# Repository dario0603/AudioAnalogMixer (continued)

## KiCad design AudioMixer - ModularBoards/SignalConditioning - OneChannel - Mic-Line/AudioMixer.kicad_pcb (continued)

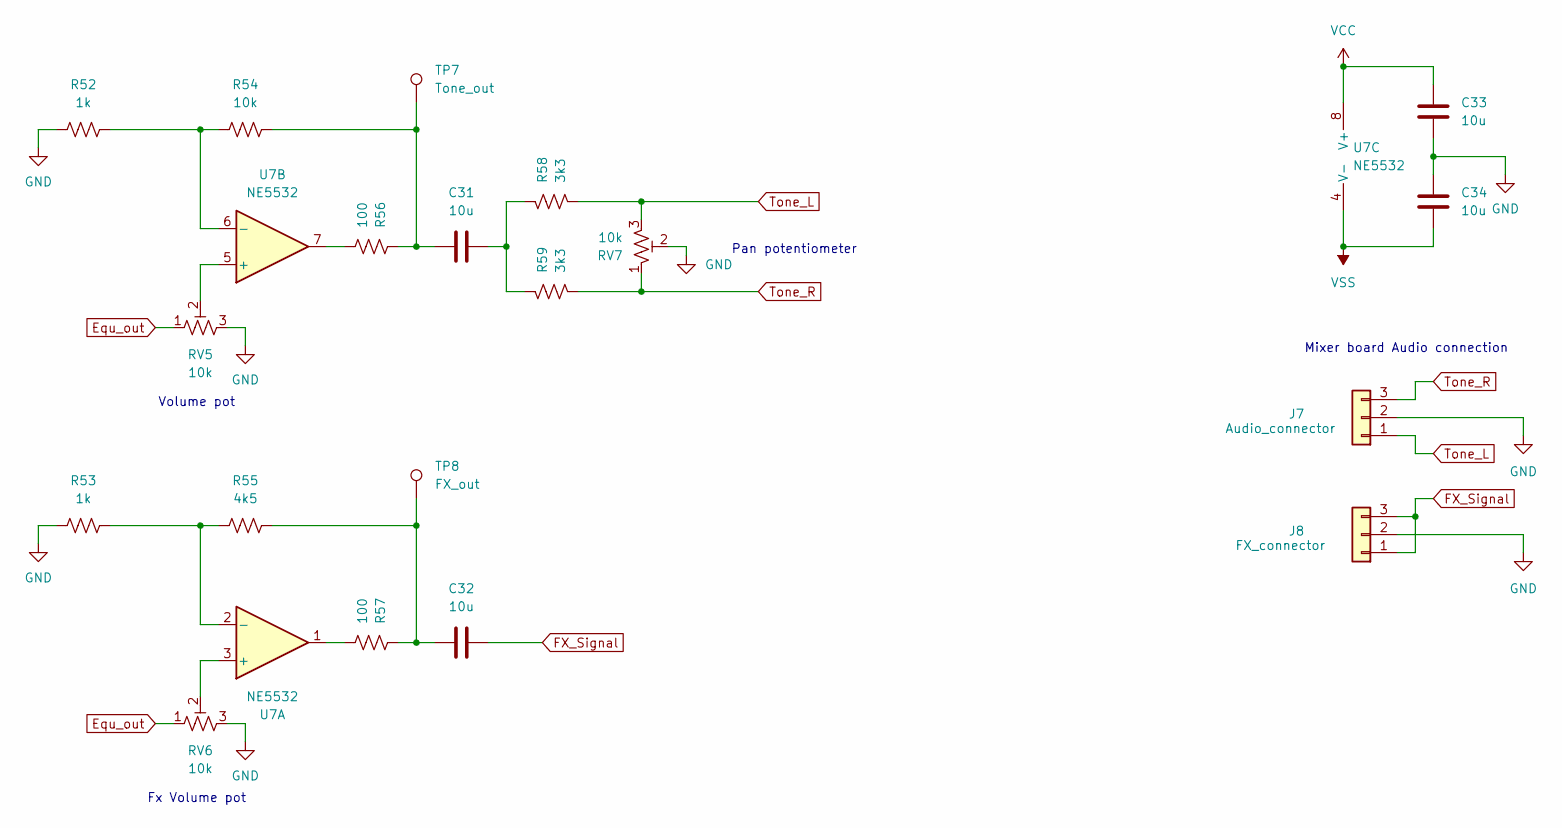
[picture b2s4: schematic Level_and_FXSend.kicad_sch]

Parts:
C31, C32, C33, C34: 10u; C_0805_2012Metric_Pad1.18x1.45mm_HandSolder
J7: Audio_connector; PinHeader_1x03_P2.54mm_Vertical
J8: FX_connector; PinHeader_1x03_P2.54mm_Vertical
R52, R53: 1k; R_0603_1608Metric_Pad0.98x0.95mm_HandSolder
R54: 10k; R_0603_1608Metric_Pad0.98x0.95mm_HandSolder
R55: 4k5; R_0603_1608Metric_Pad0.98x0.95mm_HandSolder
R56, R57: 100; R_0603_1608Metric_Pad0.98x0.95mm_HandSolder
R58, R59: 3k3; R_0603_1608Metric_Pad0.98x0.95mm_HandSolder
RV5, RV6, RV7: 10k; Potentiometer_Alps_RK097_Single_Horizontal
TP7: Tone_out; TestPoint_Pad_D1.0mm
TP8: FX_out; TestPoint_Pad_D1.0mm
U7: NE5532; SOIC-8_3.9x4.9mm_P1.27mm

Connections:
Equ_out: RV5.1, RV6.1; also elsewhere on the board
FX_Signal: C32.2, J8.1, J8.3
GND: C33.2, C34.1, J7.2, J8.2, R52.2, R53.2, RV5.3, RV6.3, RV7.2; also elsewhere on the board
unnamed: C31.1, R54.1, R56.1, TP7.1
unnamed: C31.2, R58.1, R59.1
unnamed: C32.1, R55.1, R57.1, TP8.1
unnamed: R56.2, U7.7
unnamed: R57.2, U7.1
unnamed: RV6.2, U7.3 (+)
unnamed: R53.1, R55.2, U7.2 (-)
unnamed: RV5.2, U7.5 (+)
unnamed: R52.1, R54.2, U7.6 (-)
Tone_L: J7.1, R58.2, RV7.3
Tone_R: J7.3, R59.2, RV7.1
VCC: C33.1, U7.8 (V+); also elsewhere on the board
VSS: C34.2, U7.4 (V-); also elsewhere on the board

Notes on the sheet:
Mixer board Audio connection
Volume pot
Pan potentiometer
Fx Volume pot

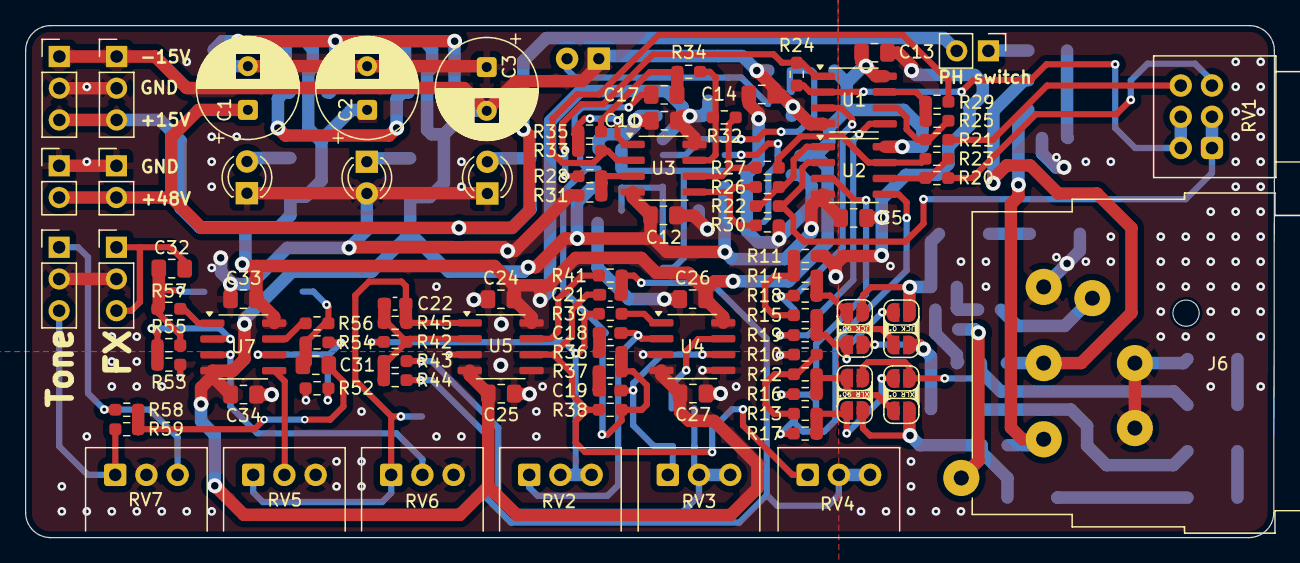
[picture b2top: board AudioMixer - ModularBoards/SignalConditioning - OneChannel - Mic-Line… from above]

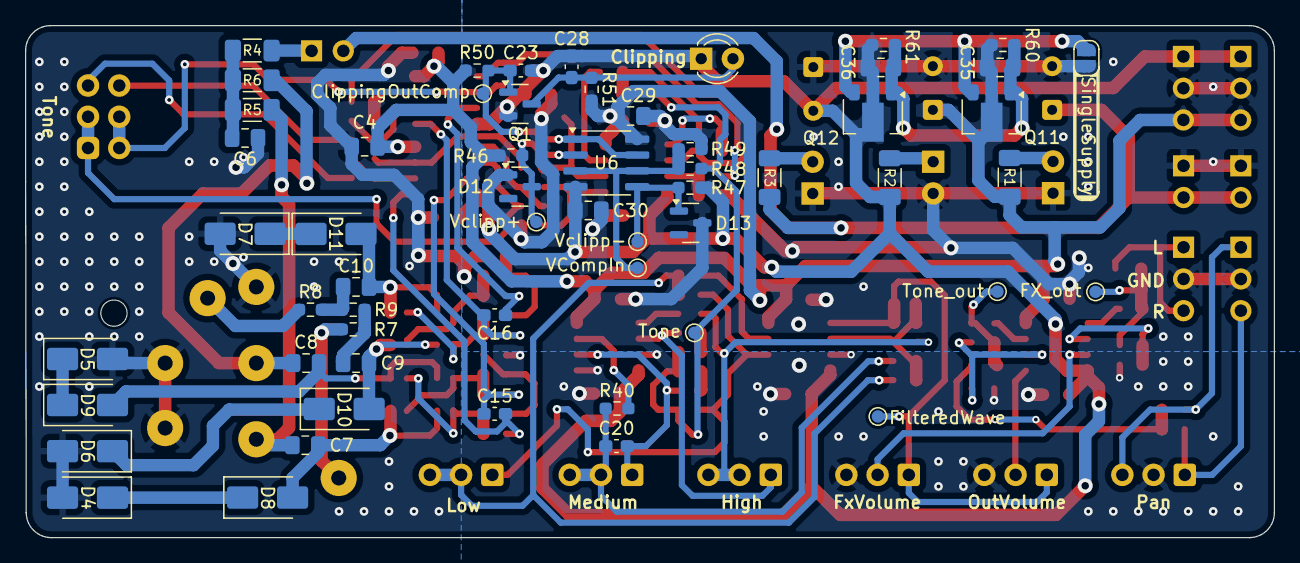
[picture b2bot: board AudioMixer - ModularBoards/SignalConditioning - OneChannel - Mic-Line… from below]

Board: 2 copper layers, 100.0 x 41.0 mm, 153 parts (57 on the bottom side), 83 nets.

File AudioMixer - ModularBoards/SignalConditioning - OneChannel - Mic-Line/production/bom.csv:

Designator,Footprint,Quantity,Value,LCSC Part #
"C1, C2, C3",CP_Radial_D8.0mm_P3.50mm,3,100u,
"C10, C17, C7, C8, C9",0805,5,22u,
"C11, C12, C13, C14, C24, C25, C26, C27, C29, C30, C31, C32, C33, C34, C35, C36, C4, C5, C6",0805,19,10u,
"C15, C16",0603,2,1n,
C18,0603,1,4n7,
C19,0603,1,40n,
"C20, C23, C28",0603,3,5n,
C21,0603,1,51n,
C22,0603,1,20p,
"D1, D14, D2, D3",LED_D3.0mm,4,LED,
"D10, D11, D4, D5, D6, D7, D8, D9",D_SMA,8,1SMA4740A,
"D12, D13",SOT-23,2,BZX84C5V1,
"J1, J3",PinHeader_1x02_P2.54mm_Vertical,2,48V_Phantom_Supply,
"J2, J4",PinHeader_1x03_P2.54mm_Vertical,2,Dual_Power_Supply,
J5,PinHeader_1x02_P2.54mm_Vertical,1,Phantom_switch,
J6,Jack_XLR-6.35mm_Neutrik_NCJ6FI-H_Horizontal,1,XLR3_AudioJack3_Combo,
J7,PinHeader_1x03_P2.54mm_Vertical,1,Audio_connector,
J8,PinHeader_1x03_P2.54mm_Vertical,1,FX_connector,
Q1,SOT-23,1,BC817,
Q11,SOT-89-3,1,BCX56,
Q12,SOT-89-3,1,BCX53,
"R1, R2",1206,2,2.2k,
"R10, R11, R20, R21, R39, R40, R41, R56, R57",0603,9,100,
"R12, R13",0603,2,2k2,
"R14, R15, R50, R60, R61",0603,5,47k,
"R16, R17, R18, R19",0603,4,220,
"R22, R23, R24, R25, R26, R27, R28, R29, R30, R31, R32, R33, R36, R37, R38, R42, R43, R44, R46, R47, R48, R49, R54",0603,23,10k,
"R3, R5, R6",1206,3,6.8k,
"R34, R35",0603,2,470,
R4,1206,1,100,
R45,0603,1,20k,
"R51, R58, R59",0603,3,3k3,
"R52, R53",0603,2,1k,
R55,0603,1,4k5,
"R7, R8",0603,2,680,
R9,0603,1,150,
RV1,Potentiometer_Alps_RK097_Dual_Horizontal,1,10k,
"RV2, RV3, RV4, RV5, RV6, RV7",Potentiometer_Alps_RK097_Single_Horizontal,6,10k,
TP1,TestPoint_Pad_D1.0mm,1,Tone,
TP2,TestPoint_Pad_D1.0mm,1,FilteredWave,
TP3,TestPoint_Pad_D1.0mm,1,VClipp+,
TP4,TestPoint_Pad_D1.0mm,1,VClipp-,
TP5,TestPoint_Pad_D1.0mm,1,VCompIn,
TP6,TestPoint_Pad_D1.0mm,1,ClippingOutComp,
TP7,TestPoint_Pad_D1.0mm,1,Tone_out,
TP8,TestPoint_Pad_D1.0mm,1,FX_out,
"U1, U2, U3, U4, U5, U7",SOIC-8_3.9x4.9mm_P1.27mm,6,NE5532,
U6,SOIC-8_3.9x4.9mm_P1.27mm,1,LM393,

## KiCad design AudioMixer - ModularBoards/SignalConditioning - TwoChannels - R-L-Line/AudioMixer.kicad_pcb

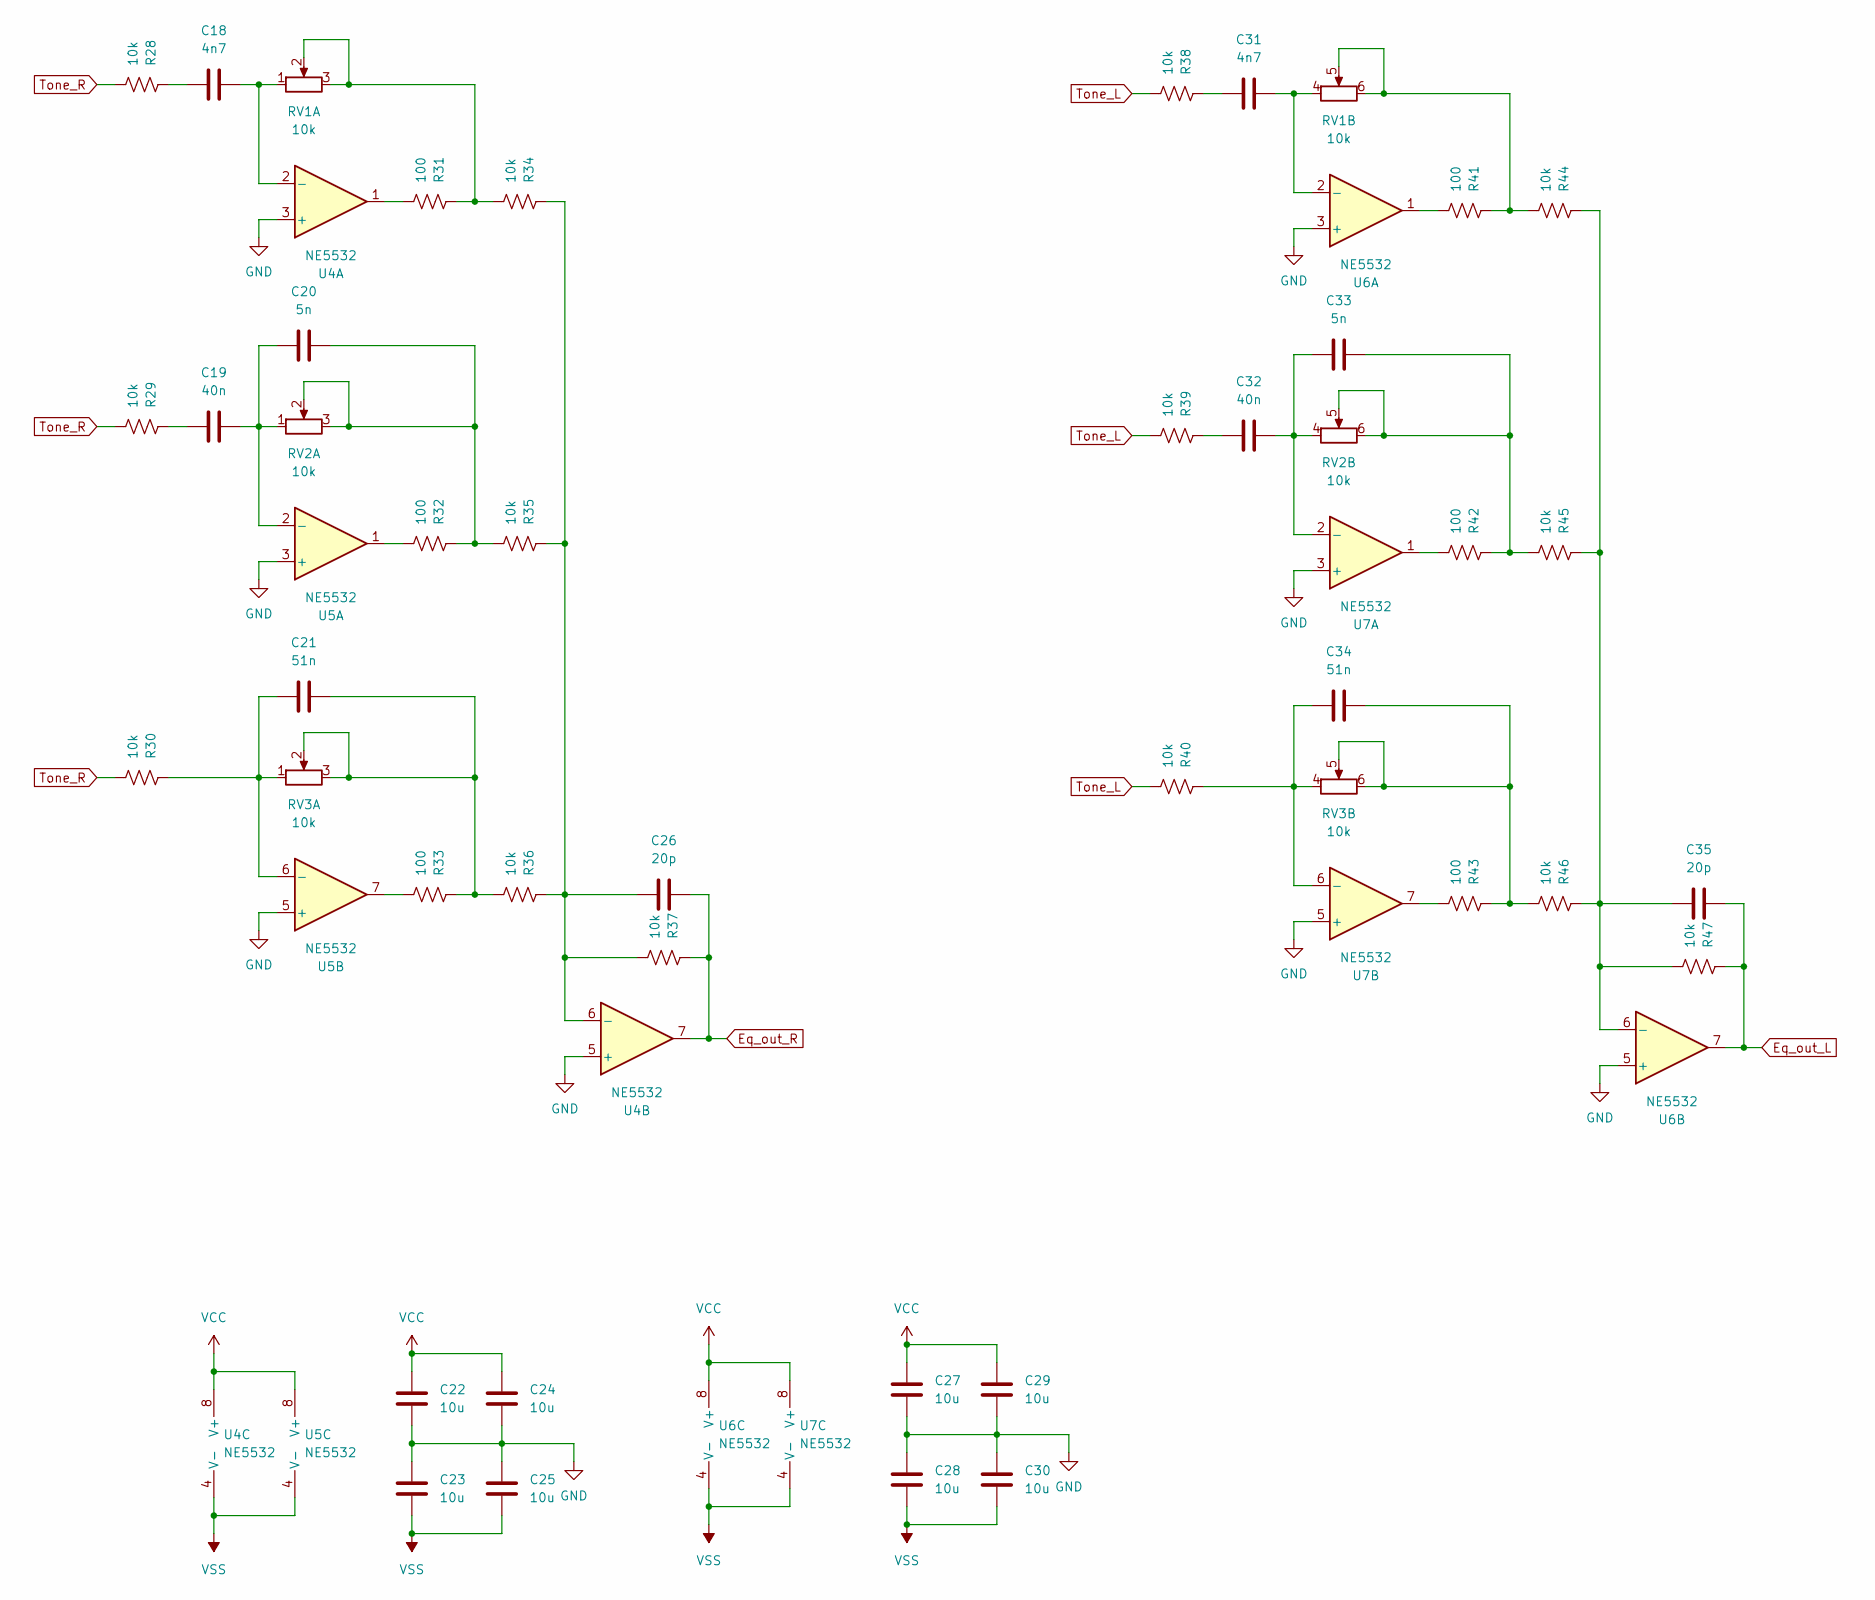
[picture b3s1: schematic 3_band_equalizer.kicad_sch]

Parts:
C18, C31: 4n7; C_0603_1608Metric_Pad1.08x0.95mm_HandSolder
C19, C32: 40n; C_0603_1608Metric_Pad1.08x0.95mm_HandSolder
C20, C33: 5n; C_0603_1608Metric_Pad1.08x0.95mm_HandSolder
C21, C34: 51n; C_0603_1608Metric_Pad1.08x0.95mm_HandSolder
C22, C23, C24, C25, C27, C28, C29, C30: 10u; C_0805_2012Metric_Pad1.18x1.45mm_HandSolder
C26, C35: 20p; C_0603_1608Metric_Pad1.08x0.95mm_HandSolder
R28, R29, R30, R34, R35, R36, R37, R38, R39, R40, R44, R45, R46, R47: 10k; R_0603_1608Metric_Pad0.98x0.95mm_HandSolder
R31, R32, R33, R41, R42, R43: 100; R_0603_1608Metric_Pad0.98x0.95mm_HandSolder
RV1, RV2, RV3: 10k; Potentiometer_Alps_RK097_Dual_Horizontal
U4, U5, U6, U7: NE5532; SOIC-8_3.9x4.9mm_P1.27mm

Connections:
Eq_out_L: C35.2, R47.1, U6.7; also elsewhere on the board
Eq_out_R: C26.2, R37.1, U4.7; also elsewhere on the board
GND: C22.2, C23.1, C24.2, C25.1, C27.2, C28.1, C29.2, C30.1, U4.3 (+), U4.5 (+), U5.3 (+), U5.5 (+), U6.3 (+), U6.5 (+), U7.3 (+), U7.5 (+); also elsewhere on the board
unnamed: C18.2, R28.1
unnamed: C19.2, R29.1
unnamed: C20.1, R32.1, R35.2, RV2.2, RV2.3
unnamed: C21.1, R33.1, R36.2, RV3.2, RV3.3
unnamed: C31.2, R38.1
unnamed: C32.2, R39.1
unnamed: C33.1, R42.1, R45.2, RV2.5, RV2.6
unnamed: C34.1, R43.1, R46.2, RV3.5, RV3.6
unnamed: R31.1, R34.2, RV1.2, RV1.3
unnamed: R31.2, U4.1
unnamed: R32.2, U5.1
unnamed: R33.2, U5.7
unnamed: R41.1, R44.2, RV1.5, RV1.6
unnamed: R41.2, U6.1
unnamed: R42.2, U7.1
unnamed: R43.2, U7.7
unnamed: C18.1, RV1.1, U4.2 (-)
unnamed: C26.1, R34.1, R35.1, R36.1, R37.2, U4.6 (-)
unnamed: C19.1, C20.2, RV2.1, U5.2 (-)
unnamed: C21.2, R30.1, RV3.1, U5.6 (-)
unnamed: C31.1, RV1.4, U6.2 (-)
unnamed: C35.1, R44.1, R45.1, R46.1, R47.2, U6.6 (-)
unnamed: C32.1, C33.2, RV2.4, U7.2 (-)
unnamed: C34.2, R40.1, RV3.4, U7.6 (-)
Tone_L: R38.2, R39.2, R40.2; also elsewhere on the board
Tone_R: R28.2, R29.2, R30.2; also elsewhere on the board
VCC: C22.1, C24.1, C27.1, C29.1, U4.8 (V+), U5.8 (V+), U6.8 (V+), U7.8 (V+); also elsewhere on the board
VSS: C23.2, C25.2, C28.2, C30.2, U4.4 (V-), U5.4 (V-), U6.4 (V-), U7.4 (V-); also elsewhere on the board

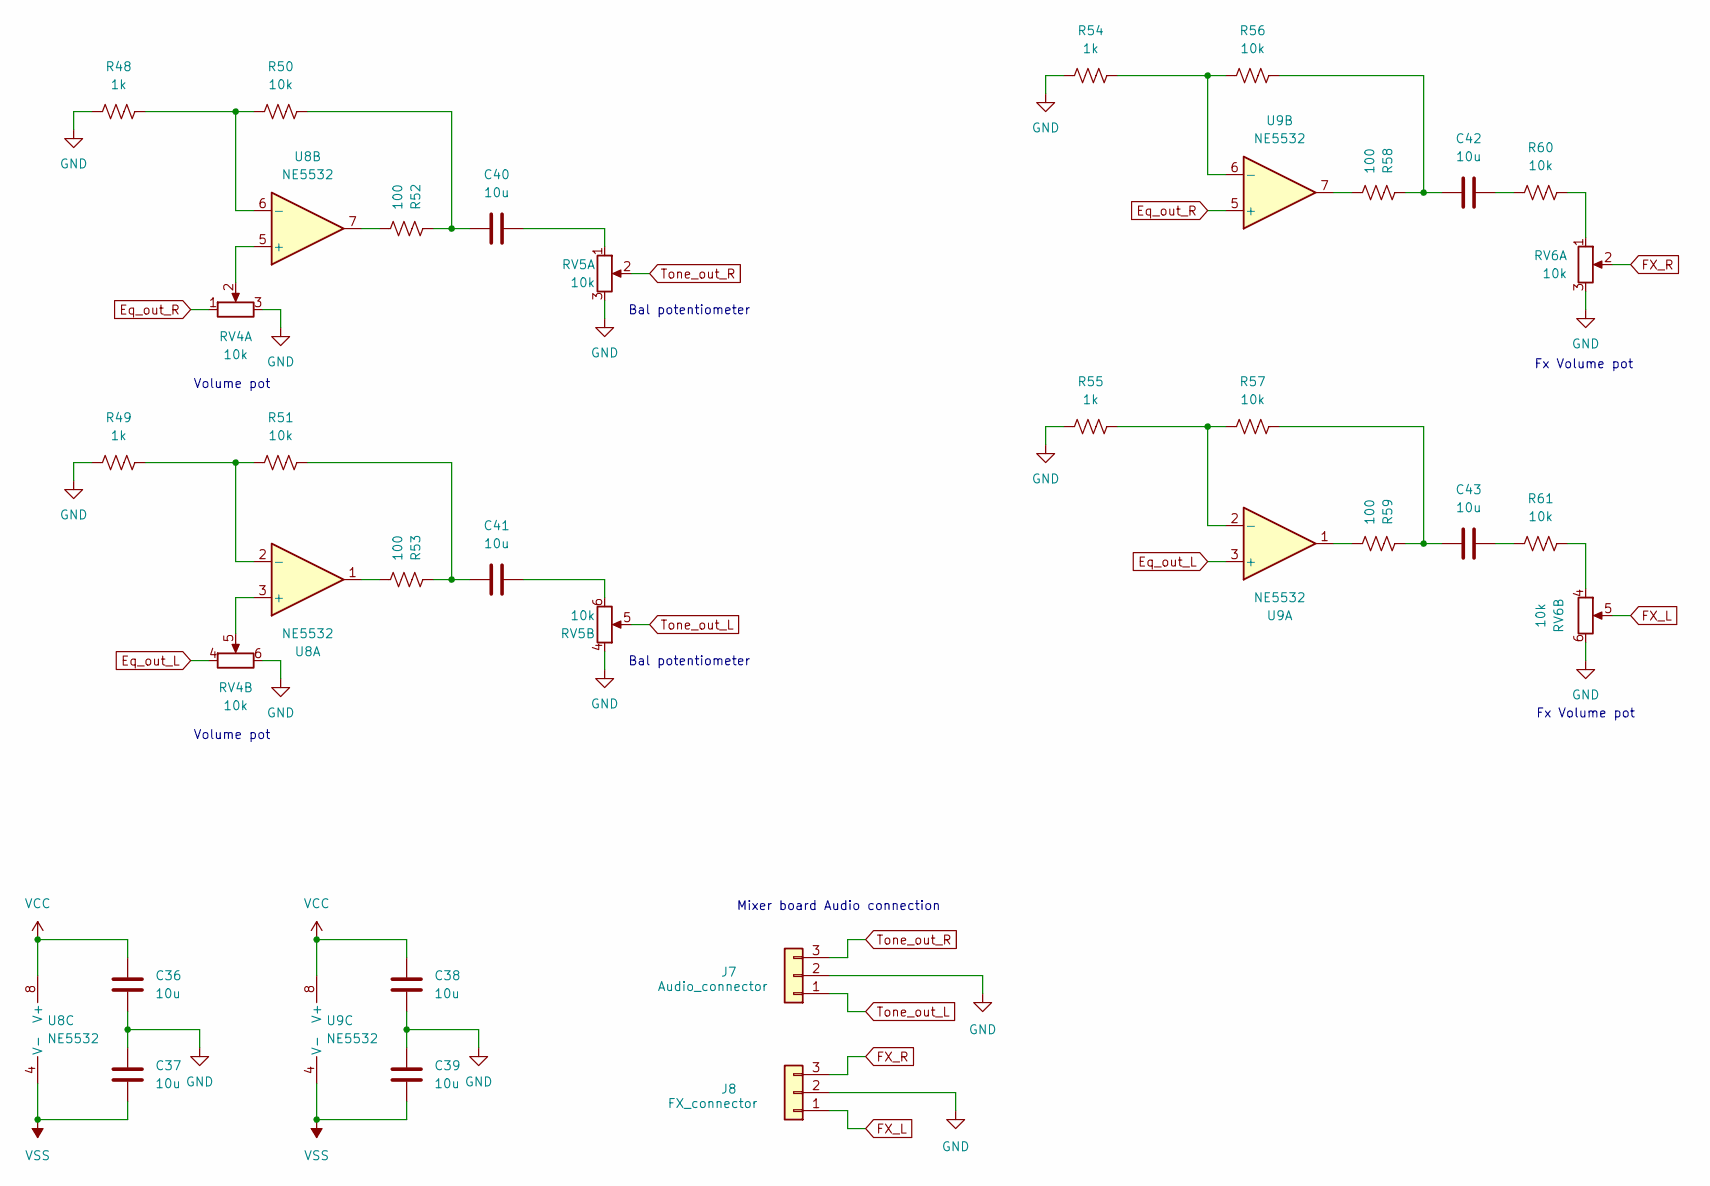
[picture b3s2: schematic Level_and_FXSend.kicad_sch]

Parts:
C36, C37, C38, C39, C40, C41, C42, C43: 10u; C_0805_2012Metric_Pad1.18x1.45mm_HandSolder
J7: Audio_connector; PinHeader_1x03_P2.54mm_Vertical
J8: FX_connector; PinHeader_1x03_P2.54mm_Vertical
R48, R49, R54, R55: 1k; R_0603_1608Metric_Pad0.98x0.95mm_HandSolder
R50, R51, R56, R57, R60, R61: 10k; R_0603_1608Metric_Pad0.98x0.95mm_HandSolder
R52, R53, R58, R59: 100; R_0603_1608Metric_Pad0.98x0.95mm_HandSolder
RV4, RV5, RV6: 10k; Potentiometer_Alps_RK097_Dual_Horizontal
U8, U9: NE5532; SOIC-8_3.9x4.9mm_P1.27mm

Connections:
Eq_out_L: RV4.4, U9.3 (+); also elsewhere on the board
Eq_out_R: RV4.1, U9.5 (+); also elsewhere on the board
FX_L: J8.1, RV6.5
FX_R: J8.3, RV6.2
GND: C36.2, C37.1, C38.2, C39.1, J7.2, J8.2, R48.2, R49.2, R54.2, R55.2, RV4.3, RV4.6, RV5.3, RV5.4, RV6.3, RV6.6; also elsewhere on the board
unnamed: C40.1, R50.1, R52.1
unnamed: C40.2, RV5.1
unnamed: C41.1, R51.1, R53.1
unnamed: C41.2, RV5.6
unnamed: C42.1, R56.1, R58.1
unnamed: C42.2, R60.2
unnamed: C43.1, R57.1, R59.1
unnamed: C43.2, R61.2
unnamed: R52.2, U8.7
unnamed: R53.2, U8.1
unnamed: R58.2, U9.7
unnamed: R59.2, U9.1
unnamed: R60.1, RV6.1
unnamed: R61.1, RV6.4
unnamed: RV4.5, U8.3 (+)
unnamed: R49.1, R51.2, U8.2 (-)
unnamed: RV4.2, U8.5 (+)
unnamed: R48.1, R50.2, U8.6 (-)
unnamed: R55.1, R57.2, U9.2 (-)
unnamed: R54.1, R56.2, U9.6 (-)
Tone_out_L: J7.1, RV5.5
Tone_out_R: J7.3, RV5.2
VCC: C36.1, C38.1, U8.8 (V+), U9.8 (V+); also elsewhere on the board
VSS: C37.2, C39.2, U8.4 (V-), U9.4 (V-); also elsewhere on the board

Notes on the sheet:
Bal potentiometer
Volume pot
Mixer board Audio connection
Fx Volume pot

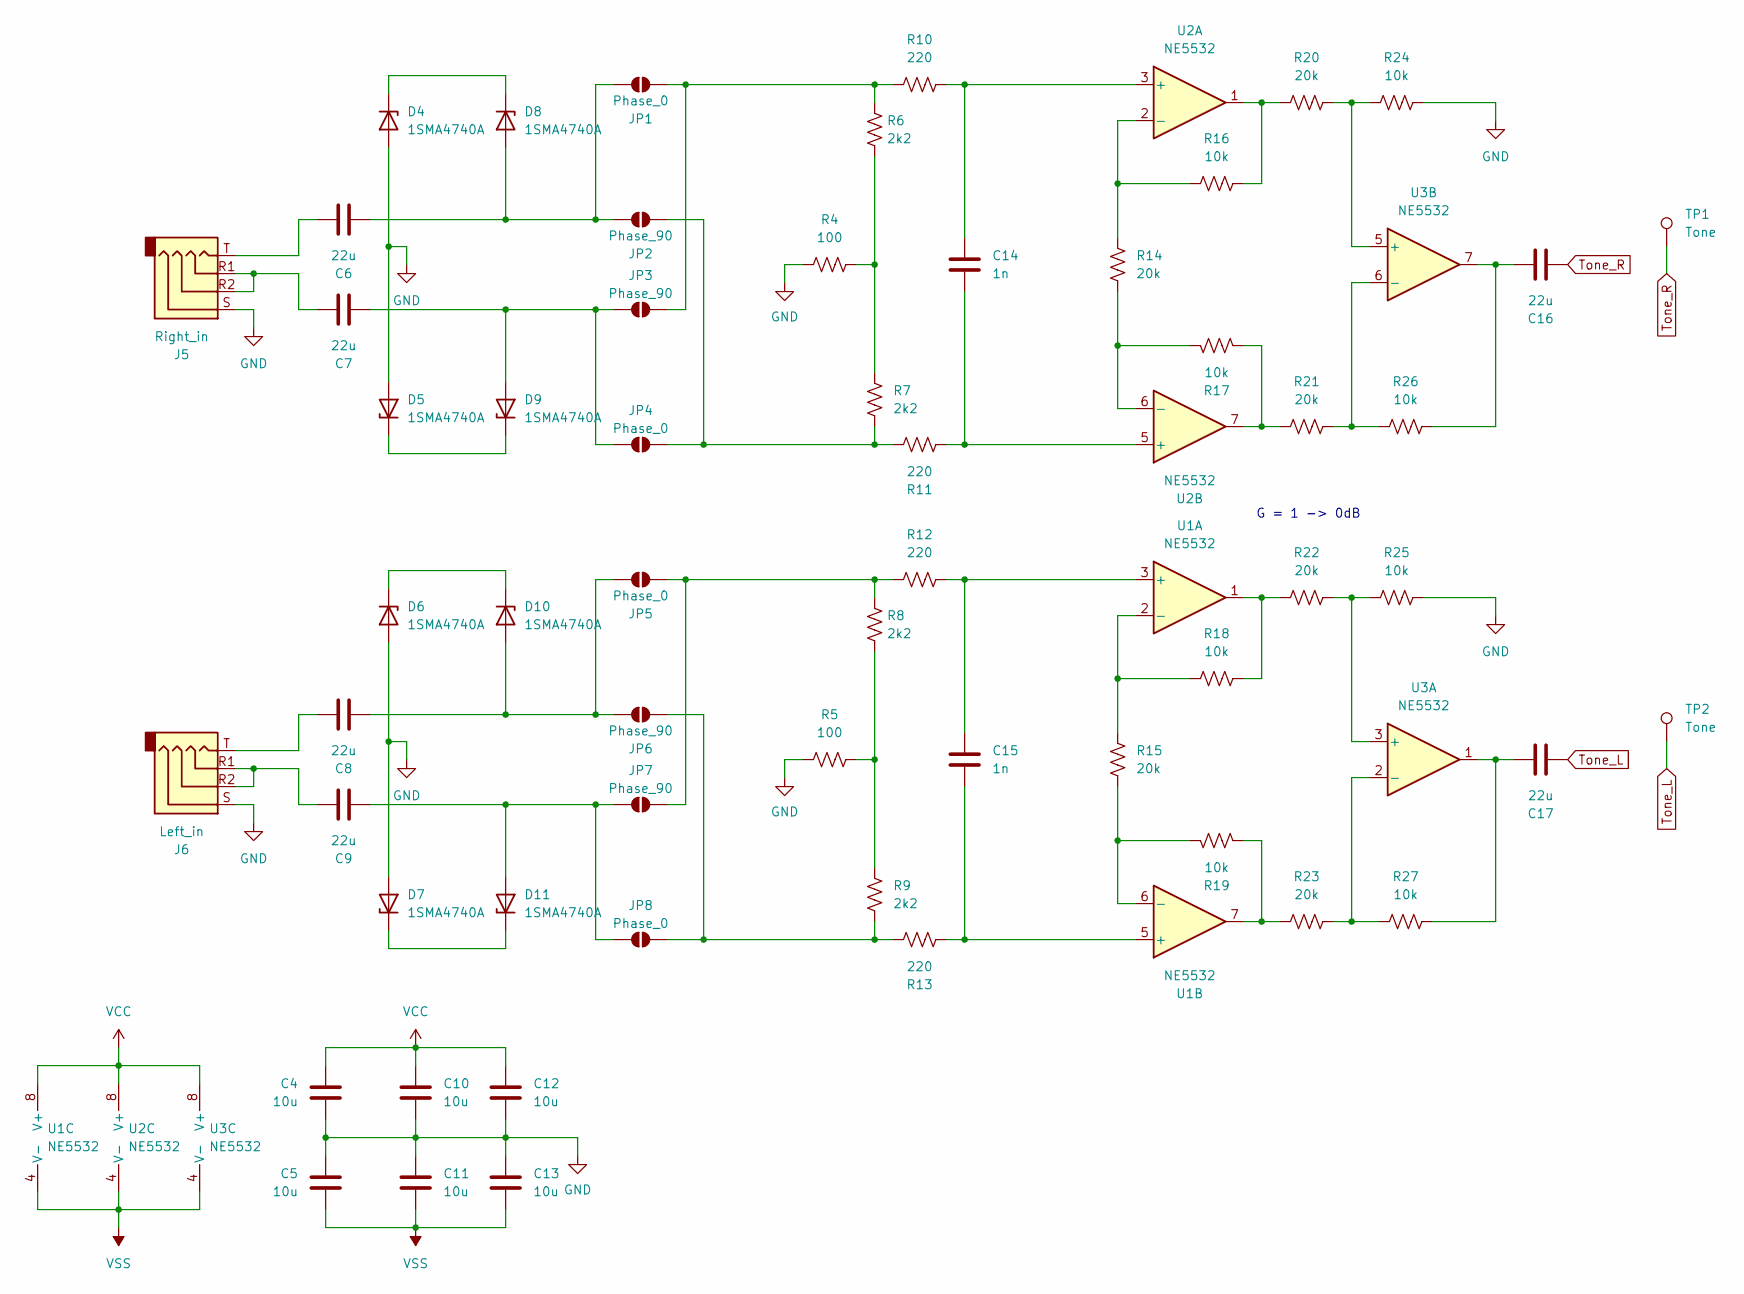
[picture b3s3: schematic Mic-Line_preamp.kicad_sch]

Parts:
C4, C5, C10, C11, C12, C13: 10u; C_0805_2012Metric_Pad1.18x1.45mm_HandSolder
C6, C7, C8, C9, C16, C17: 22u; C_0805_2012Metric_Pad1.18x1.45mm_HandSolder
C14, C15: 1n; C_0603_1608Metric_Pad1.08x0.95mm_HandSolder
D4, D5, D6, D7, D8, D9, D10, D11: 1SMA4740A; D_SMA
J5: Right_in; Jack_3.5mm_PJ320E_Horizontal
J6: Left_in; Jack_3.5mm_PJ320E_Horizontal
JP1, JP4, JP5, JP8: Phase_0; SolderJumper-2_P1.3mm_Open_RoundedPad1.0x1.5mm
JP2, JP3, JP6, JP7: Phase_90; SolderJumper-2_P1.3mm_Open_RoundedPad1.0x1.5mm
R4, R5: 100; R_0603_1608Metric_Pad0.98x0.95mm_HandSolder
R6, R7, R8, R9: 2k2; R_0603_1608Metric_Pad0.98x0.95mm_HandSolder
R10, R11, R12, R13: 220; R_0603_1608Metric_Pad0.98x0.95mm_HandSolder
R14, R15, R20, R21, R22, R23: 20k; R_0603_1608Metric_Pad0.98x0.95mm_HandSolder
R16, R17, R18, R19, R24, R25, R26, R27: 10k; R_0603_1608Metric_Pad0.98x0.95mm_HandSolder
TP1, TP2: Tone; TestPoint_Pad_D1.0mm
U1, U2, U3: NE5532; SOIC-8_3.9x4.9mm_P1.27mm

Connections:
GND: C4.2, C5.1, C10.2, C11.1, C12.2, C13.1, D4.2 (A), D5.2 (A), D6.2 (A), D7.2 (A), J5.S, J6.S, R4.1, R5.1, R24.1, R25.1; also elsewhere on the board
unnamed: C6.1, J5.T
unnamed: C7.1, J5.R1, J5.R2
unnamed: C8.1, J6.T
unnamed: C9.1, J6.R1, J6.R2
unnamed: C16.1, R26.1, U3.7
unnamed: C17.1, R27.1, U3.1
unnamed: D4.1 (K), D8.1 (K)
unnamed: D5.1 (K), D9.1 (K)
unnamed: C6.2, D8.2 (A), JP1.1 (A), JP2.1 (A)
unnamed: C7.2, D9.2 (A), JP3.1 (A), JP4.1 (A)
unnamed: C8.2, D10.2 (A), JP5.1 (A), JP6.1 (A)
unnamed: D6.1 (K), D10.1 (K)
unnamed: C9.2, D11.2 (A), JP7.1 (A), JP8.1 (A)
unnamed: D7.1 (K), D11.1 (K)
unnamed: JP1.2 (B), JP3.2 (B), R6.1, R10.2
unnamed: JP2.2 (B), JP4.2 (B), R7.2, R11.1
unnamed: JP5.2 (B), JP7.2 (B), R8.1, R12.2
unnamed: JP6.2 (B), JP8.2 (B), R9.2, R13.1
unnamed: R4.2, R6.2, R7.1
unnamed: R5.2, R8.2, R9.1
unnamed: R16.1, R20.1, U2.1
unnamed: R17.1, R21.1, U2.7
unnamed: R18.1, R22.1, U1.1
unnamed: R19.1, R23.1, U1.7
unnamed: C15.1, R12.1, U1.3 (+)
unnamed: R15.1, R18.2, U1.2 (-)
unnamed: C15.2, R13.2, U1.5 (+)
unnamed: R15.2, R19.2, U1.6 (-)
unnamed: C14.1, R10.1, U2.3 (+)
unnamed: R14.1, R16.2, U2.2 (-)
unnamed: C14.2, R11.2, U2.5 (+)
unnamed: R14.2, R17.2, U2.6 (-)
unnamed: R22.2, R25.2, U3.3 (+)
unnamed: R23.2, R27.2, U3.2 (-)
unnamed: R20.2, R24.2, U3.5 (+)
unnamed: R21.2, R26.2, U3.6 (-)
Tone_L: C17.2, TP2.1; also elsewhere on the board
Tone_R: C16.2, TP1.1; also elsewhere on the board
VCC: C4.1, C10.1, C12.1, U1.8 (V+), U2.8 (V+), U3.8 (V+); also elsewhere on the board
VSS: C5.2, C11.2, C13.2, U1.4 (V-), U2.4 (V-), U3.4 (V-); also elsewhere on the board

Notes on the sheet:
G = 1 -> 0dB

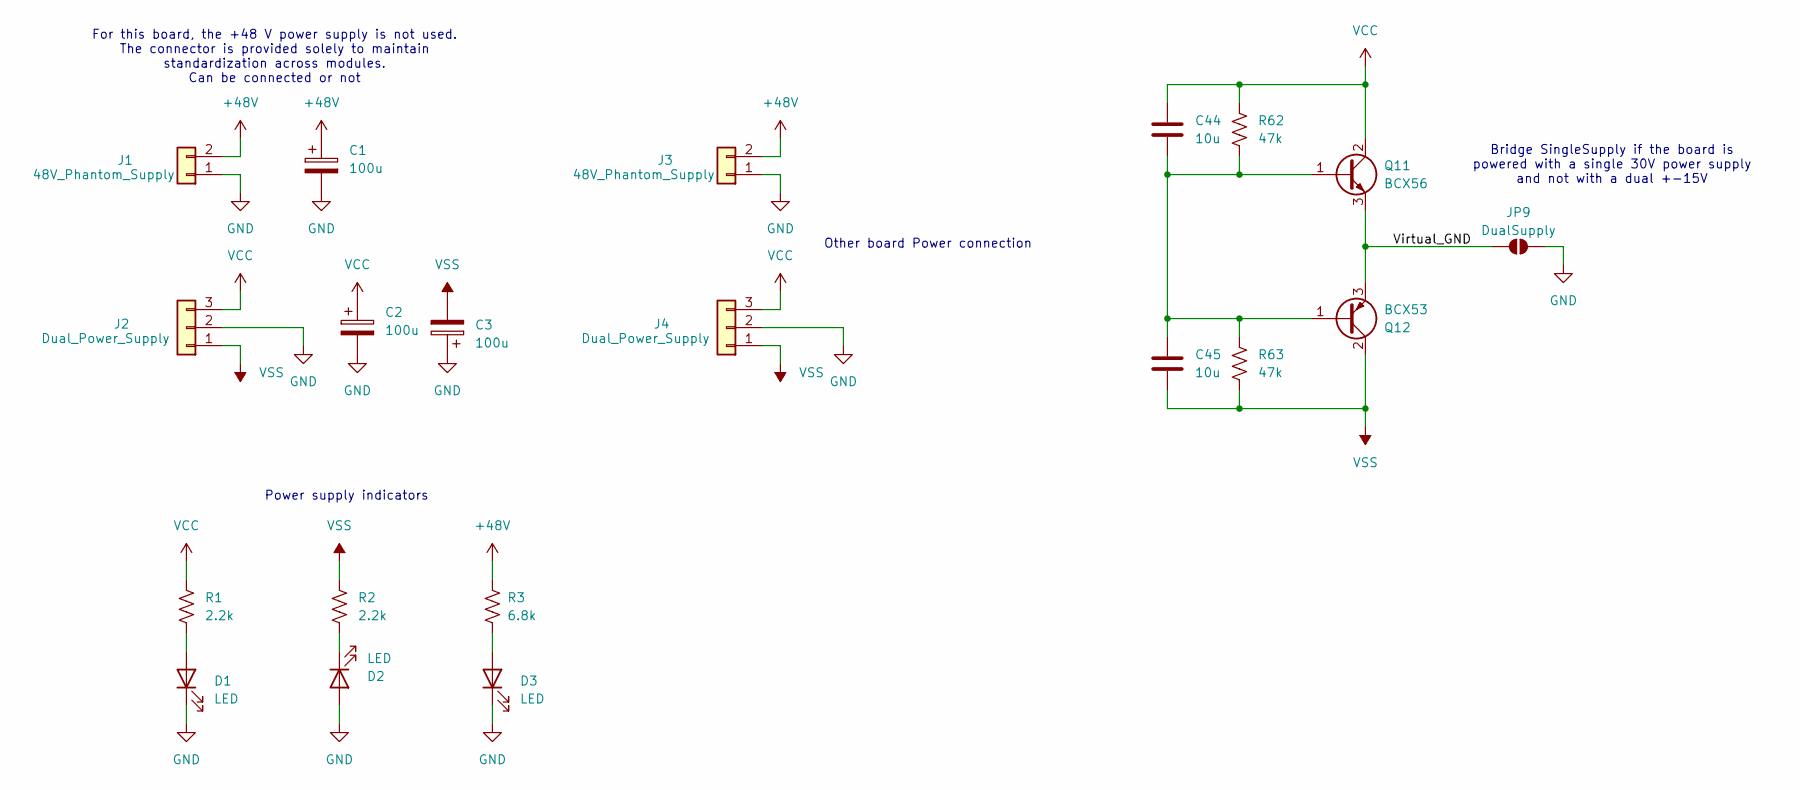
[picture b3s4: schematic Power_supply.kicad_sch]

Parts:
C1, C2, C3: 100u; CP_Radial_D8.0mm_P3.50mm
C44, C45: 10u; C_0805_2012Metric_Pad1.18x1.45mm_HandSolder
D1, D2, D3: LED; LED_D3.0mm
J1, J3: 48V_Phantom_Supply; PinHeader_1x02_P2.54mm_Vertical
J2, J4: Dual_Power_Supply; PinHeader_1x03_P2.54mm_Vertical
JP9: DualSupply; SolderJumper-2_P1.3mm_Open_RoundedPad1.0x1.5mm
Q11: BCX56; SOT-89-3
Q12: BCX53; SOT-89-3
R1, R2: 2.2k; R_1206_3216Metric_Pad1.30x1.75mm_HandSolder
R3: 6.8k; R_1206_3216Metric_Pad1.30x1.75mm_HandSolder
R62, R63: 47k; R_0603_1608Metric_Pad0.98x0.95mm_HandSolder

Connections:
+48V: C1.1, J1.2, J3.2, R3.2
/Power supply/Virtual_GND: JP9.1 (A), Q11.3 (E), Q12.3 (E)
GND: C1.2, C2.2, C3.1, D1.1 (K), D2.2 (A), D3.1 (K), J1.1, J2.2, J3.1, J4.2, JP9.2 (B); also elsewhere on the board
unnamed: D1.2 (A), R1.1
unnamed: D2.1 (K), R2.1
unnamed: D3.2 (A), R3.1
unnamed: C44.2, C45.1, Q11.1 (B), Q12.1 (B), R62.2, R63.1
VCC: C2.1, C44.1, J2.3, J4.3, Q11.2 (C), R1.2, R62.1; also elsewhere on the board
VSS: C3.2, C45.2, J2.1, J4.1, Q12.2 (C), R2.2, R63.2; also elsewhere on the board

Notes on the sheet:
Other board Power connection
For this board, the +48 V power supply is not used. The connector is provided solely to maintain standardization across modules. Can be connected or not
Power supply indicators
Bridge SingleSupply if the board is powered with a single 30V power supply and not with a dual +-15V

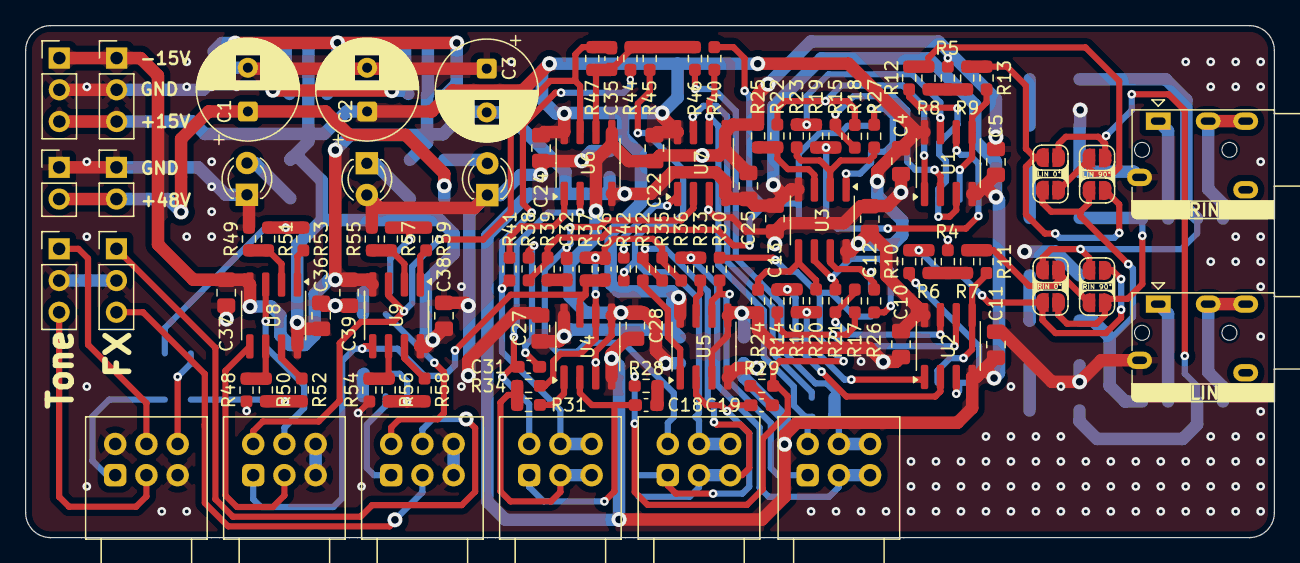
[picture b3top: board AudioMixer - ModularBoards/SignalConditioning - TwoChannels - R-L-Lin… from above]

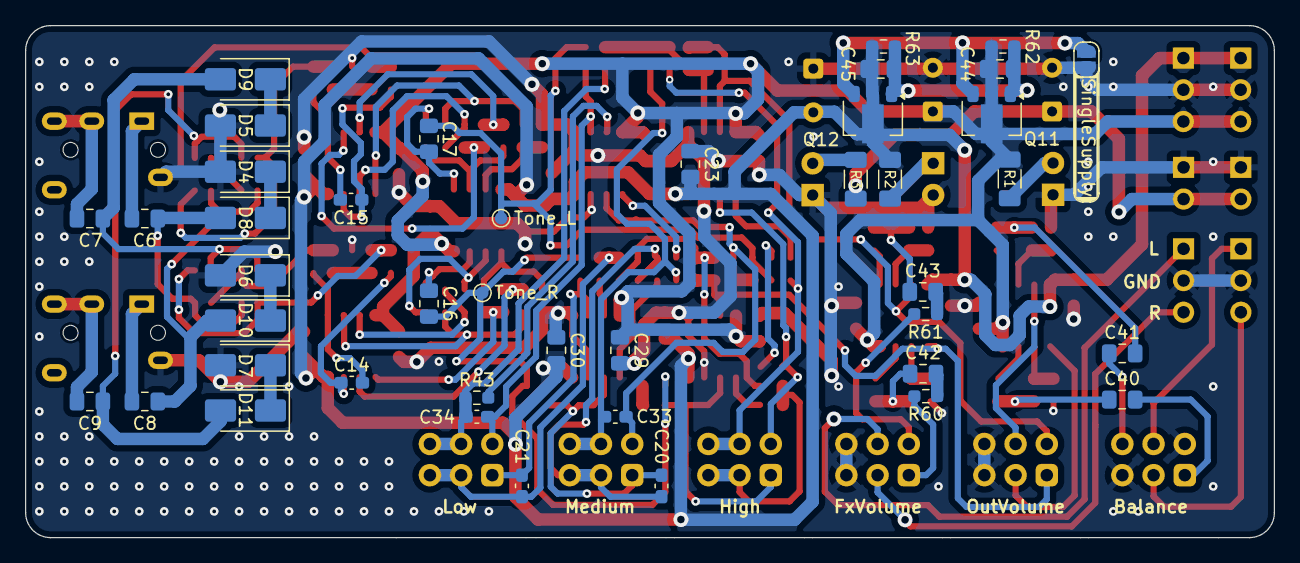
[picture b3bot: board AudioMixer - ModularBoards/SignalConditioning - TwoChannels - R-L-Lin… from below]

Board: 2 copper layers, 100.0 x 41.0 mm, 155 parts (42 on the bottom side), 97 nets.
